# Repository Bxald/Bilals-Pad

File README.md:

**Bilal’s MacroPad**  
It is my first ever engineering-related project and I think I did really good. It consists of 6 keys using Seeed XIAO RP2040 with a rotary encoder and 128x64 OLED display.

It will be helping me making my time more efficient and help me in tasks that are very common but are taking too much time off my schedule \+ I can always change its code to program it the way I want.

**Features:** 

* 6 MX-style keys (in a 3×2 layout)  
* EC11 rotary encoder  
  (Rotate: Volume Up / Down  
  Press: Mute)  
* 0.91” 128×64 OLED display

(- Shows volume level  
\- Encoder press state  
\- Last key pressed)

* Direct GPIO wiring  
* Macro-ready firmware \- keys can be easily remapped  
* No RGB \- clean, simple, and functional (and maybe minimalistic)

**CAD Model:**  
The model is really simple, just using the simple guide. Top and bottom part held together with 4 M3 screws and headset inserts while having cut-outs for 6 switches, a rotary knob and the display. 

It has 2 separate printed parts, a bottom base that holds the pcb and everything on top while the top plate hides it all.

Made in Fusion360 (using it for the first time btw :\>). I noticed it right now that I didn’t add the 3D model of XIAO RP 2040 (I wonder if it even exists)   
**PCB:**  
Here is my PCB\! I made it myself in KiCad with the help of a tutorial at HackClub and some google too\! It is a 2 layered PCB board with through-hole XIAO RP2040, 6 switches, a rotary knob and an OLED display. 

Schematic

PCB  
**Firmware:**  
This hackpad uses KMK firmware for everything, written in CircuitPython it can handle 6 keys functions (which is really easy to change, just edit it in keyboard.keymap in [main.py](http://main.py)), a rotary knob for volume up/down and pressing it down mutes the volume and an OLED showing volume level, encoder press state and the last key pressed.

## **Bill of Materials (BOM)**

* 1× Seeed XIAO RP2040 (through-hole)  
* 6× MX-style mechanical switches  
* 6× Blank DSA keycaps (white)  
* 1× EC11 rotary encoder  
* 1× 0.91” OLED display (128×64, I²C)  
* 4× M3×16mm screws  
* 4× M3 heatset inserts  
* 1× 3D printed case (top \+ bottom)  
* Custom PCB (2-layer)  
* CircuitPython \+ KMK firmware

## **Notes**

* No RGB LEDs were used in this design.  
* All parts comply with the provided allowed materials list (by hackclub).  
* The project stays within all size and input limits.

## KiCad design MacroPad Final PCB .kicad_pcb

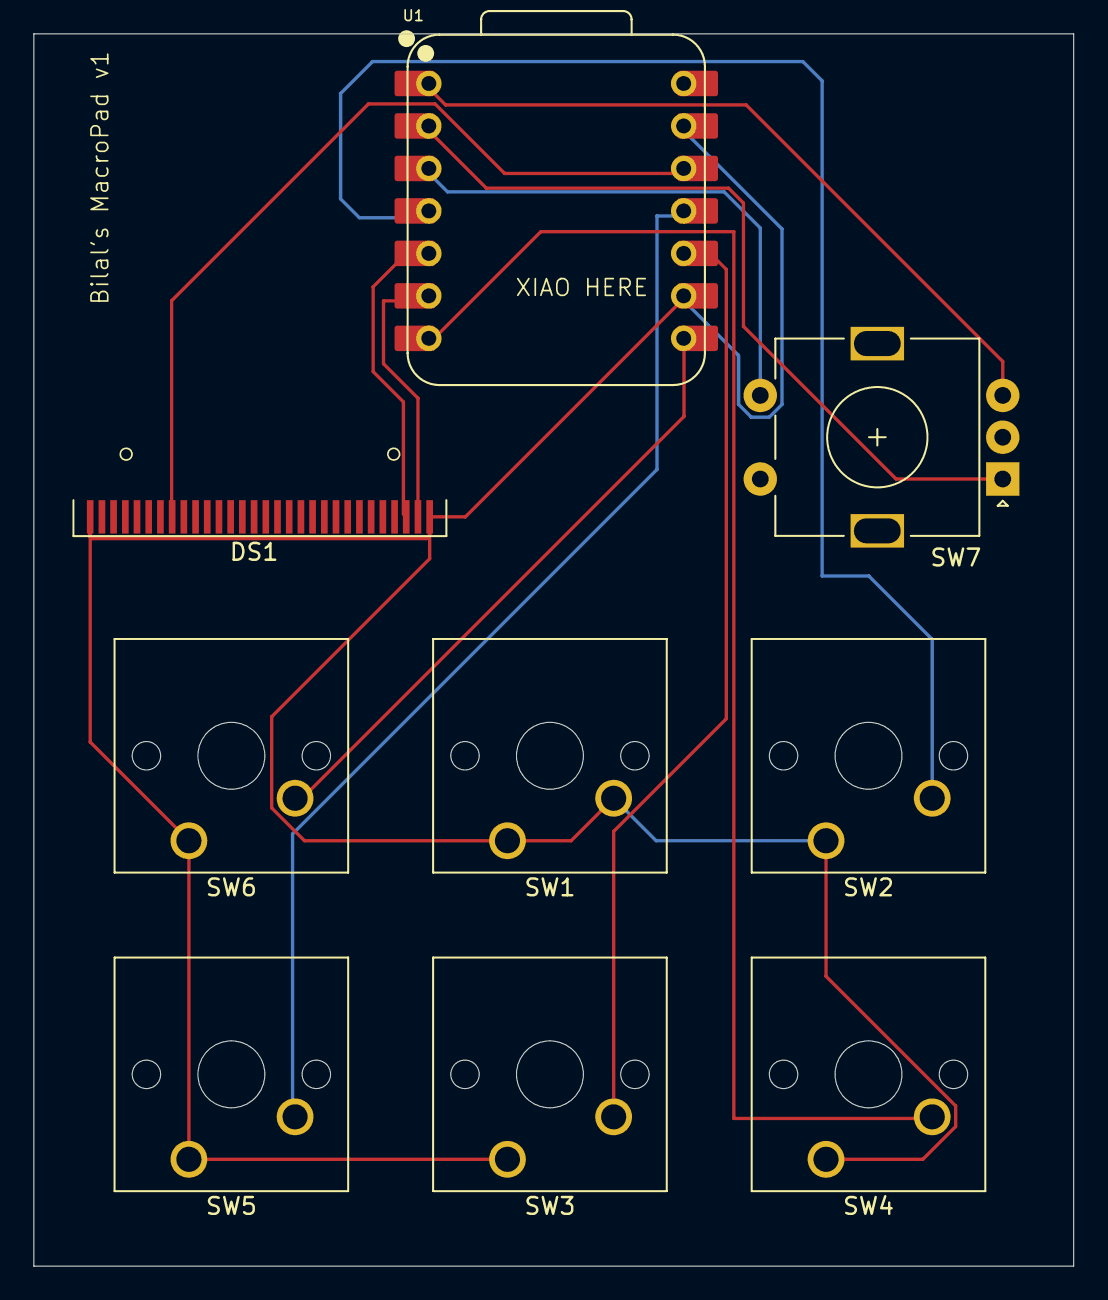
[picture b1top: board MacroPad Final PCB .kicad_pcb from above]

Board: 2 copper layers, 62.2 x 73.7 mm, 9 parts (0 on the bottom side), 11 nets.

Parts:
DS1: OLED-128O064D
SW1, SW2, SW3, SW4, SW5, SW6: SW_Push; SW_Cherry_MX_1.00u_PCB
SW7: RotaryEncoder_Switch; RotaryEncoder_Alps_EC11E-Switch_Vertical_H20mm
U1: XIAO-RP2040-DIP

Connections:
+3.3V: DS1.8 (VCC), U1.12 (3V3)
GND: DS1.1 (GND), DS1.30 (GND), SW1.1, SW1.2, SW2.1, SW3.1, SW4.1, SW5.1, SW6.1, U1.9 (GPIO2/SCK), U1.13 (GND)
unnamed: DS1.29 (SCL), U1.6 (GPIO7/SCL)
unnamed: DS1.28 (SDA), U1.5 (GPIO6/SDA)
unnamed: SW4.2, U1.7 (GPIO0/TX)
unnamed: SW6.2, U1.8 (GPIO1/RX)
unnamed: SW3.2, U1.10 (GPIO4/MISO)
unnamed: SW7.B, U1.1 (GPIO26/ADC0/A0)
unnamed: SW7.A, U1.2 (GPIO27/ADC1/A1)
unnamed: SW7.S1, U1.3 (GPIO28/ADC2/A2)
unnamed: SW2.2, U1.4 (GPIO29/ADC3/A3)

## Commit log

2025-12-21 Create CAD
